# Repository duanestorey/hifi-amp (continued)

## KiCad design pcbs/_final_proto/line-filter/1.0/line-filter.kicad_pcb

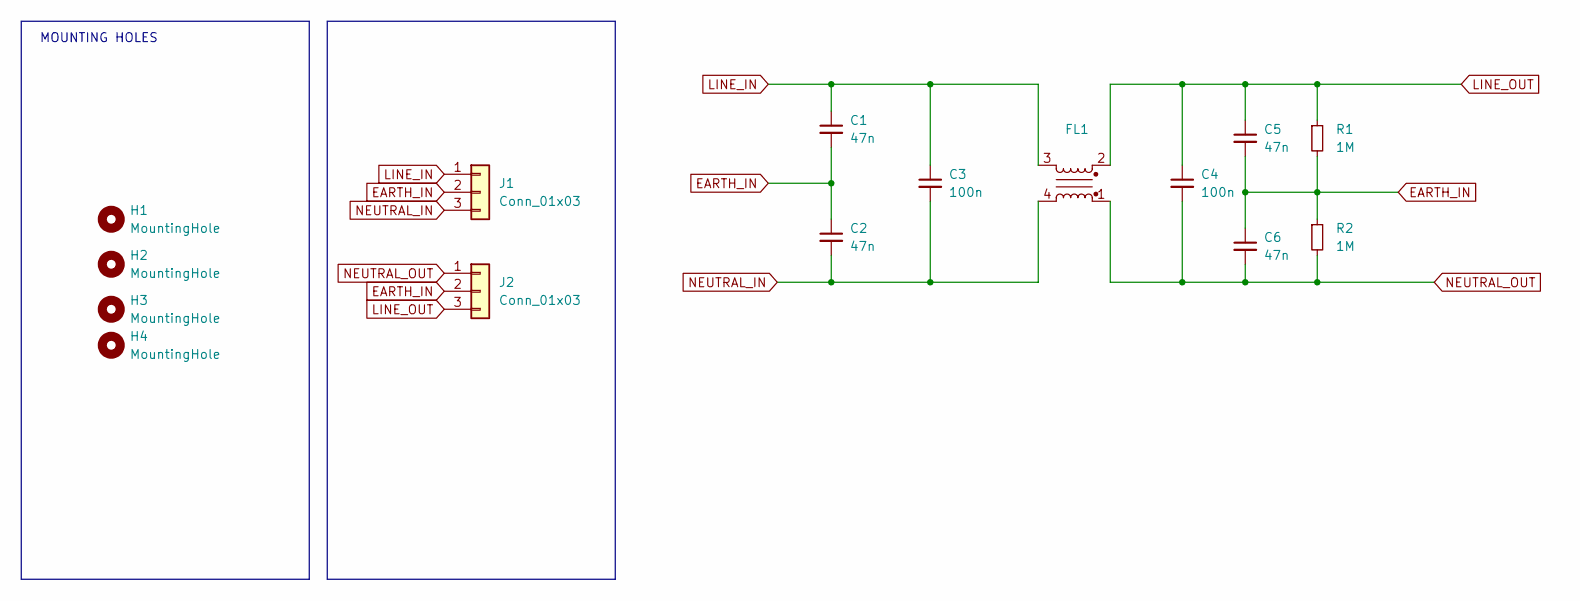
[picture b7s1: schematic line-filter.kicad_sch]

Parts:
C1, C2, C5, C6: 47n; C_Rect_L18.0mm_W7.0mm_P15.00mm_FKS3_FKP3
C3, C4: 100n; C_Rect_L18.0mm_W5.0mm_P15.00mm_FKS3_FKP3
FL1: Choke_CommonMode_PulseElectronics_PH9455x356NL; SSR21NV-M
H1, H2, H3, H4: MountingHole; MountingHole_3.2mm_M3_DIN965_Pad_TopBottom
J1, J2: Conn_01x03; TerminalBlock_Phoenix_MKDS-1,5-3_1x03_P5.00mm_Horizontal
R1, R2: 1M; R_1206_3216Metric_Pad1.30x1.75mm_HandSolder

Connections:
EARTH_IN: C1.2, C2.1, C5.2, C6.1, J1.2, J2.2, R1.2, R2.1
LINE_IN: C1.1, C3.1, FL1.3, J1.1
LINE_OUT: C4.1, C5.1, FL1.2, J2.3, R1.1
NEUTRAL_IN: C2.2, C3.2, FL1.4, J1.3
NEUTRAL_OUT: C4.2, C6.2, FL1.1, J2.1, R2.2

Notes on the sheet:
MOUNTING HOLES

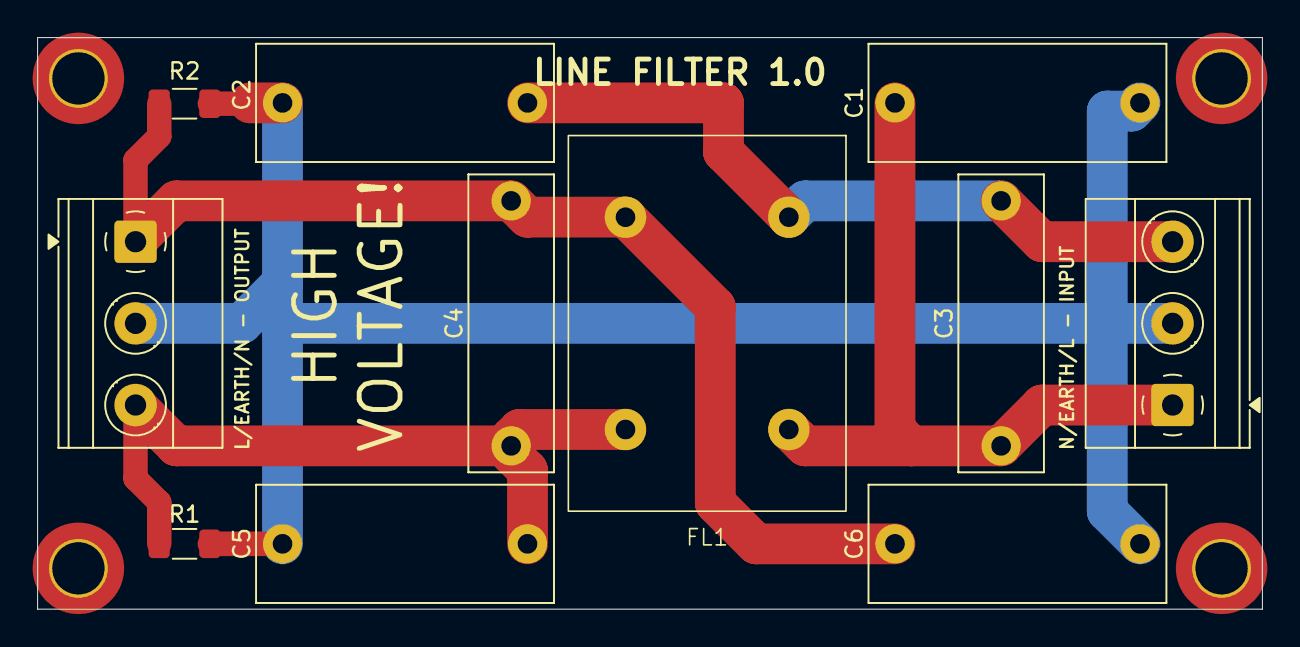
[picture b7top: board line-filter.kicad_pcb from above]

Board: 2 copper layers, 75.0 x 35.0 mm, 15 parts (0 on the bottom side), 5 nets.
